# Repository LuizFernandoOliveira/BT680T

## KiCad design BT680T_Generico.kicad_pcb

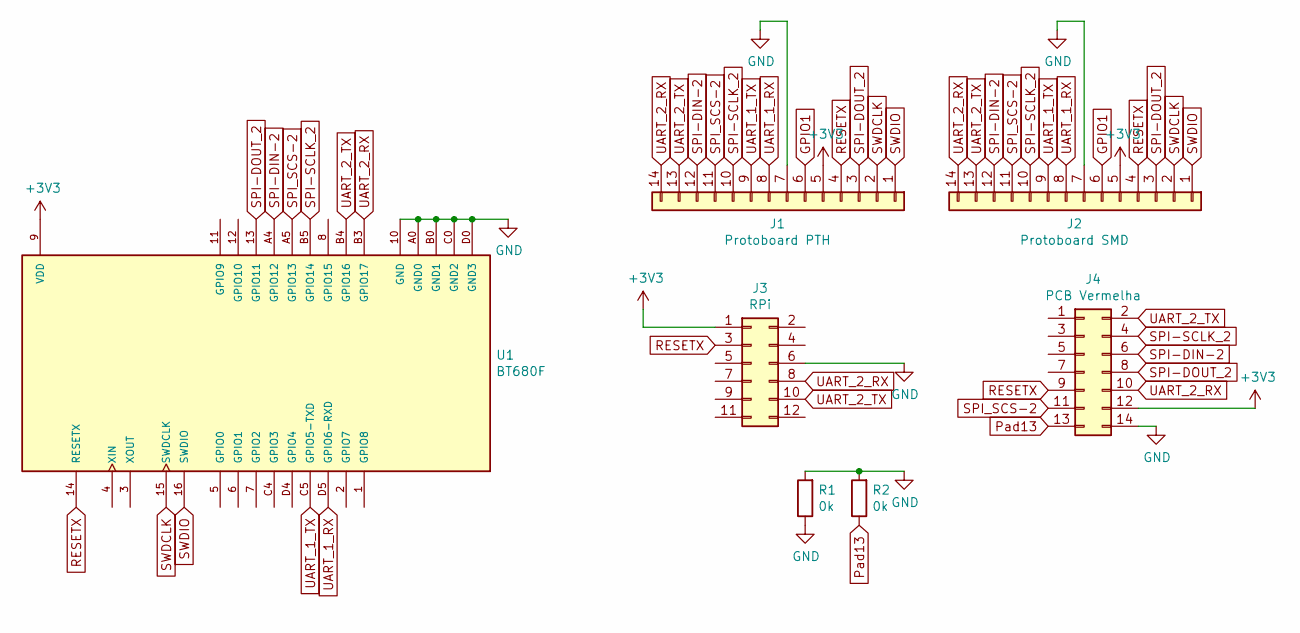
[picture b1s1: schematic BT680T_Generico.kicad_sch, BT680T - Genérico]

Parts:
J1: Protoboard PTH; PinSocket_1x14_P2.54mm_Vertical
J2: Protoboard SMD; PinSocket_1x14_P2.54mm_Vertical
J3: RPi; PinSocket_2x06_P2.54mm_Vertical
J4: PCB Vermelha; PinSocket_2x07_P2.54mm_Vertical
R1, R2: 0k; R_0805_2012Metric
U1: BT680F; MODULE_BT680F; PARTREV June 2019, Ver. 1.00

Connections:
+3V3: J1.5, J2.5, J3.1, J4.12, U1.9 (VDD)
GND: J1.7, J2.7, J3.6, J4.14, R1.1, R1.2, R2.2, U1.10 (GND), U1.A0 (GND0), U1.B0 (GND1), U1.C0 (GND2), U1.D0 (GND3)
GPIO1: J1.6, J2.6
Pad13: J4.13, R2.1
RESETX: J1.4, J2.4, J3.3, J4.9, U1.14 (RESETX)
SPI-DIN-2: J1.12, J2.12, J4.6, U1.A4 (GPIO12)
SPI-DOUT_2: J1.3, J2.3, J4.8, U1.13 (GPIO11)
SPI-SCLK_2: J1.10, J2.10, J4.4, U1.B5 (GPIO14)
SPI_SCS-2: J1.11, J2.11, J4.11, U1.A5 (GPIO13)
SWDCLK: J1.2, J2.2, U1.15 (SWDCLK)
SWDIO: J1.1, J2.1, U1.16 (SWDIO)
UART_1_RX: J1.8, J2.8, U1.D5 (GPIO6-RXD)
UART_1_TX: J1.9, J2.9, U1.C5 (GPIO5-TXD)
UART_2_RX: J1.14, J2.14, J3.8, J4.10, U1.B3 (GPIO17)
UART_2_TX: J1.13, J2.13, J3.10, J4.2, U1.B4 (GPIO16)

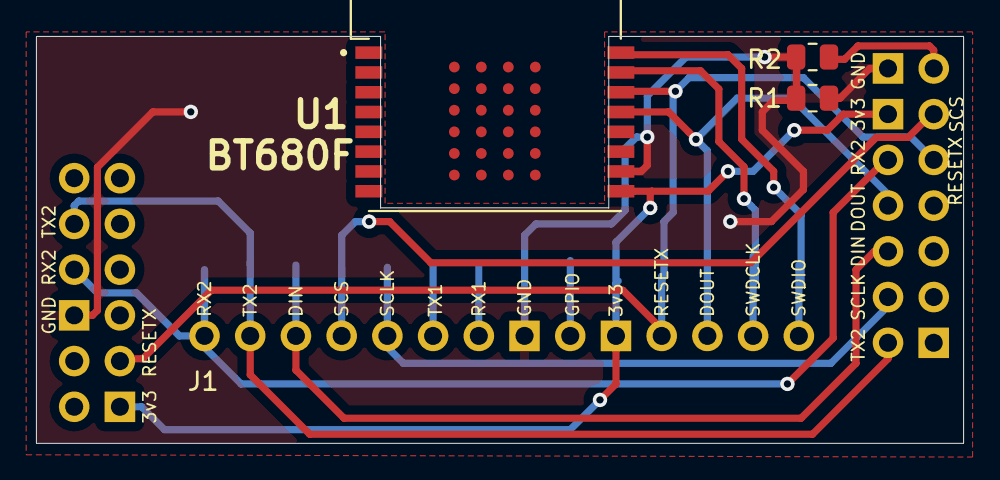
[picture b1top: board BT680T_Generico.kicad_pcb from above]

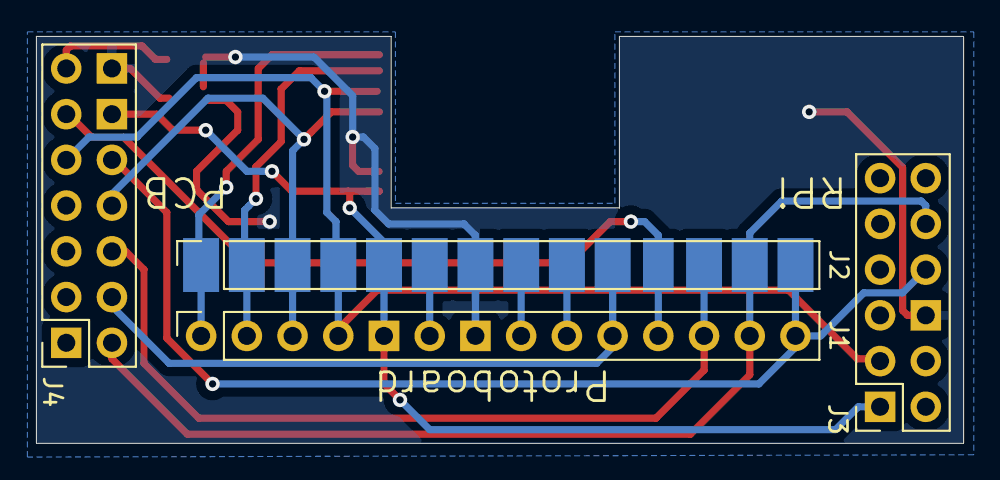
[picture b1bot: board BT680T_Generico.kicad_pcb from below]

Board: 2 copper layers, 51.5 x 22.6 mm, 7 parts (4 on the bottom side), 15 nets.

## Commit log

2024-01-28 Initial version
